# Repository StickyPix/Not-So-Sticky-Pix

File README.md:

# StickyPix

StickyPix is a small, rechargeable e-paper picture frame that lets you send
images from a phone or desktop app over Bluetooth Low Energy. The same product
family supports a four-gray black-and-white display and a six-color display.

## Image gallery

<table>
  <tr>
    <td></td>
    <td></td>
    <td></td>
  </tr>
  <tr>
    <td></td>
    <td></td>
    <td></td>
  </tr>
  <tr>
    <td></td>
    <td></td>
    <td></td>
  </tr>
</table>

## What is in this repository?

StickyPix is developed as a complete hardware and software product:

| Area | Contents |
| --- | --- |
| App | Flutter image editor, dithering previews, device management, and BLE image transfer |
| Firmware | Zephyr-based firmware for four-gray and six-color display variants |
| Hardware | KiCad schematics, PCBs, fabrication outputs, and bills of materials |
| Enclosure | Blender source files and printable STL parts for the bezel, rear shell, inner enclosure, and kickstand |
| Images | Prototype photos and product renders |

## How it works

1. Choose an image in the Flutter app.
2. Crop, rotate, and adjust the image for the selected device.
3. The app converts the image to the display's limited palette using dithering.
4. The processed framebuffer is sent to the device over BLE.
5. The device refreshes the e-paper panel and returns transfer progress and battery information.

The image pipeline currently supports:

- Four-gray output for the black-and-white display variant.
- Six-color output for black, white, yellow, red, blue, and green.
- Portrait and landscape editing for the six-color device.
- Packed framebuffer transfer sized for the target panel.

## Display variants

- [Six-color display / Spectra 6 panel](https://www.ebay.com/itm/267508191177?var=567305393025)
- [Black-and-white display panel](https://www.good-display.com/product/613.html)

The linked vendor pages are the reference parts for the current hardware
designs. Check the vendor documentation for the latest availability and
electrical specifications before ordering.

## JLCPCB fabrication settings

For the current PCB designs, I use the following JLCPCB configuration as the
fabrication reference:

| Setting | Value |
| --- | --- |
| Design | 1 |
| Delivery format | Single PCB |
| PCB thickness | 1.0 mm |
| PCB color | Green |
| Silkscreen | White |
| Material | FR4 TG135 |
| Surface finish | HASL (with lead) |
| Outer copper | 1 oz |
| Inner copper | 0.5 oz |
| Specify layer sequence | No |
| Specify stackup | Yes |
| Layer stackup | JLC04101H-3313 |

Treat this as the current ordering reference, not a guarantee that every board
revision uses the same stackup. Recheck the board layer count, dimensions, and
JLCPCB options before placing an order.

## Enclosure

The enclosure is split into a front bezel, rear shell, inner cardstock/support
piece, and kickstand. The repository includes both the editable Blender model
and exported STL files.

<table>
  <tr>
    <td></td>
    <td></td>
    <td></td>
  </tr>
</table>

## Repository layout

```text
Images/                         Prototype photos
3D Model/                       Printable enclosure STL files
Hardware/24p_bw_3p5/            Black-and-white KiCad design
Hardware/50p_spectra6_4/        Six-color KiCad design
Firmware/4GrayFinal/             Four-gray Zephyr firmware
Firmware/6ColorFinal/            Six-color Zephyr firmware
Flutter App/frontend/sticky_pix/ Flutter application
Manufacturing/                  Manufacturing files and BOM
```

## Project status

StickyPix is an active hardware prototype. The app, firmware, PCB designs, and
enclosure are included for development and iteration; dimensions, pinouts,
image timings, and manufacturing outputs may change.

## Development notes

The Flutter application is in `Flutter App/frontend/sticky_pix`. The firmware
projects use Zephyr and are kept separate so the four-gray and six-color panel
drivers can evolve independently. Build-tool-generated files and local SDK
paths should remain uncommitted.

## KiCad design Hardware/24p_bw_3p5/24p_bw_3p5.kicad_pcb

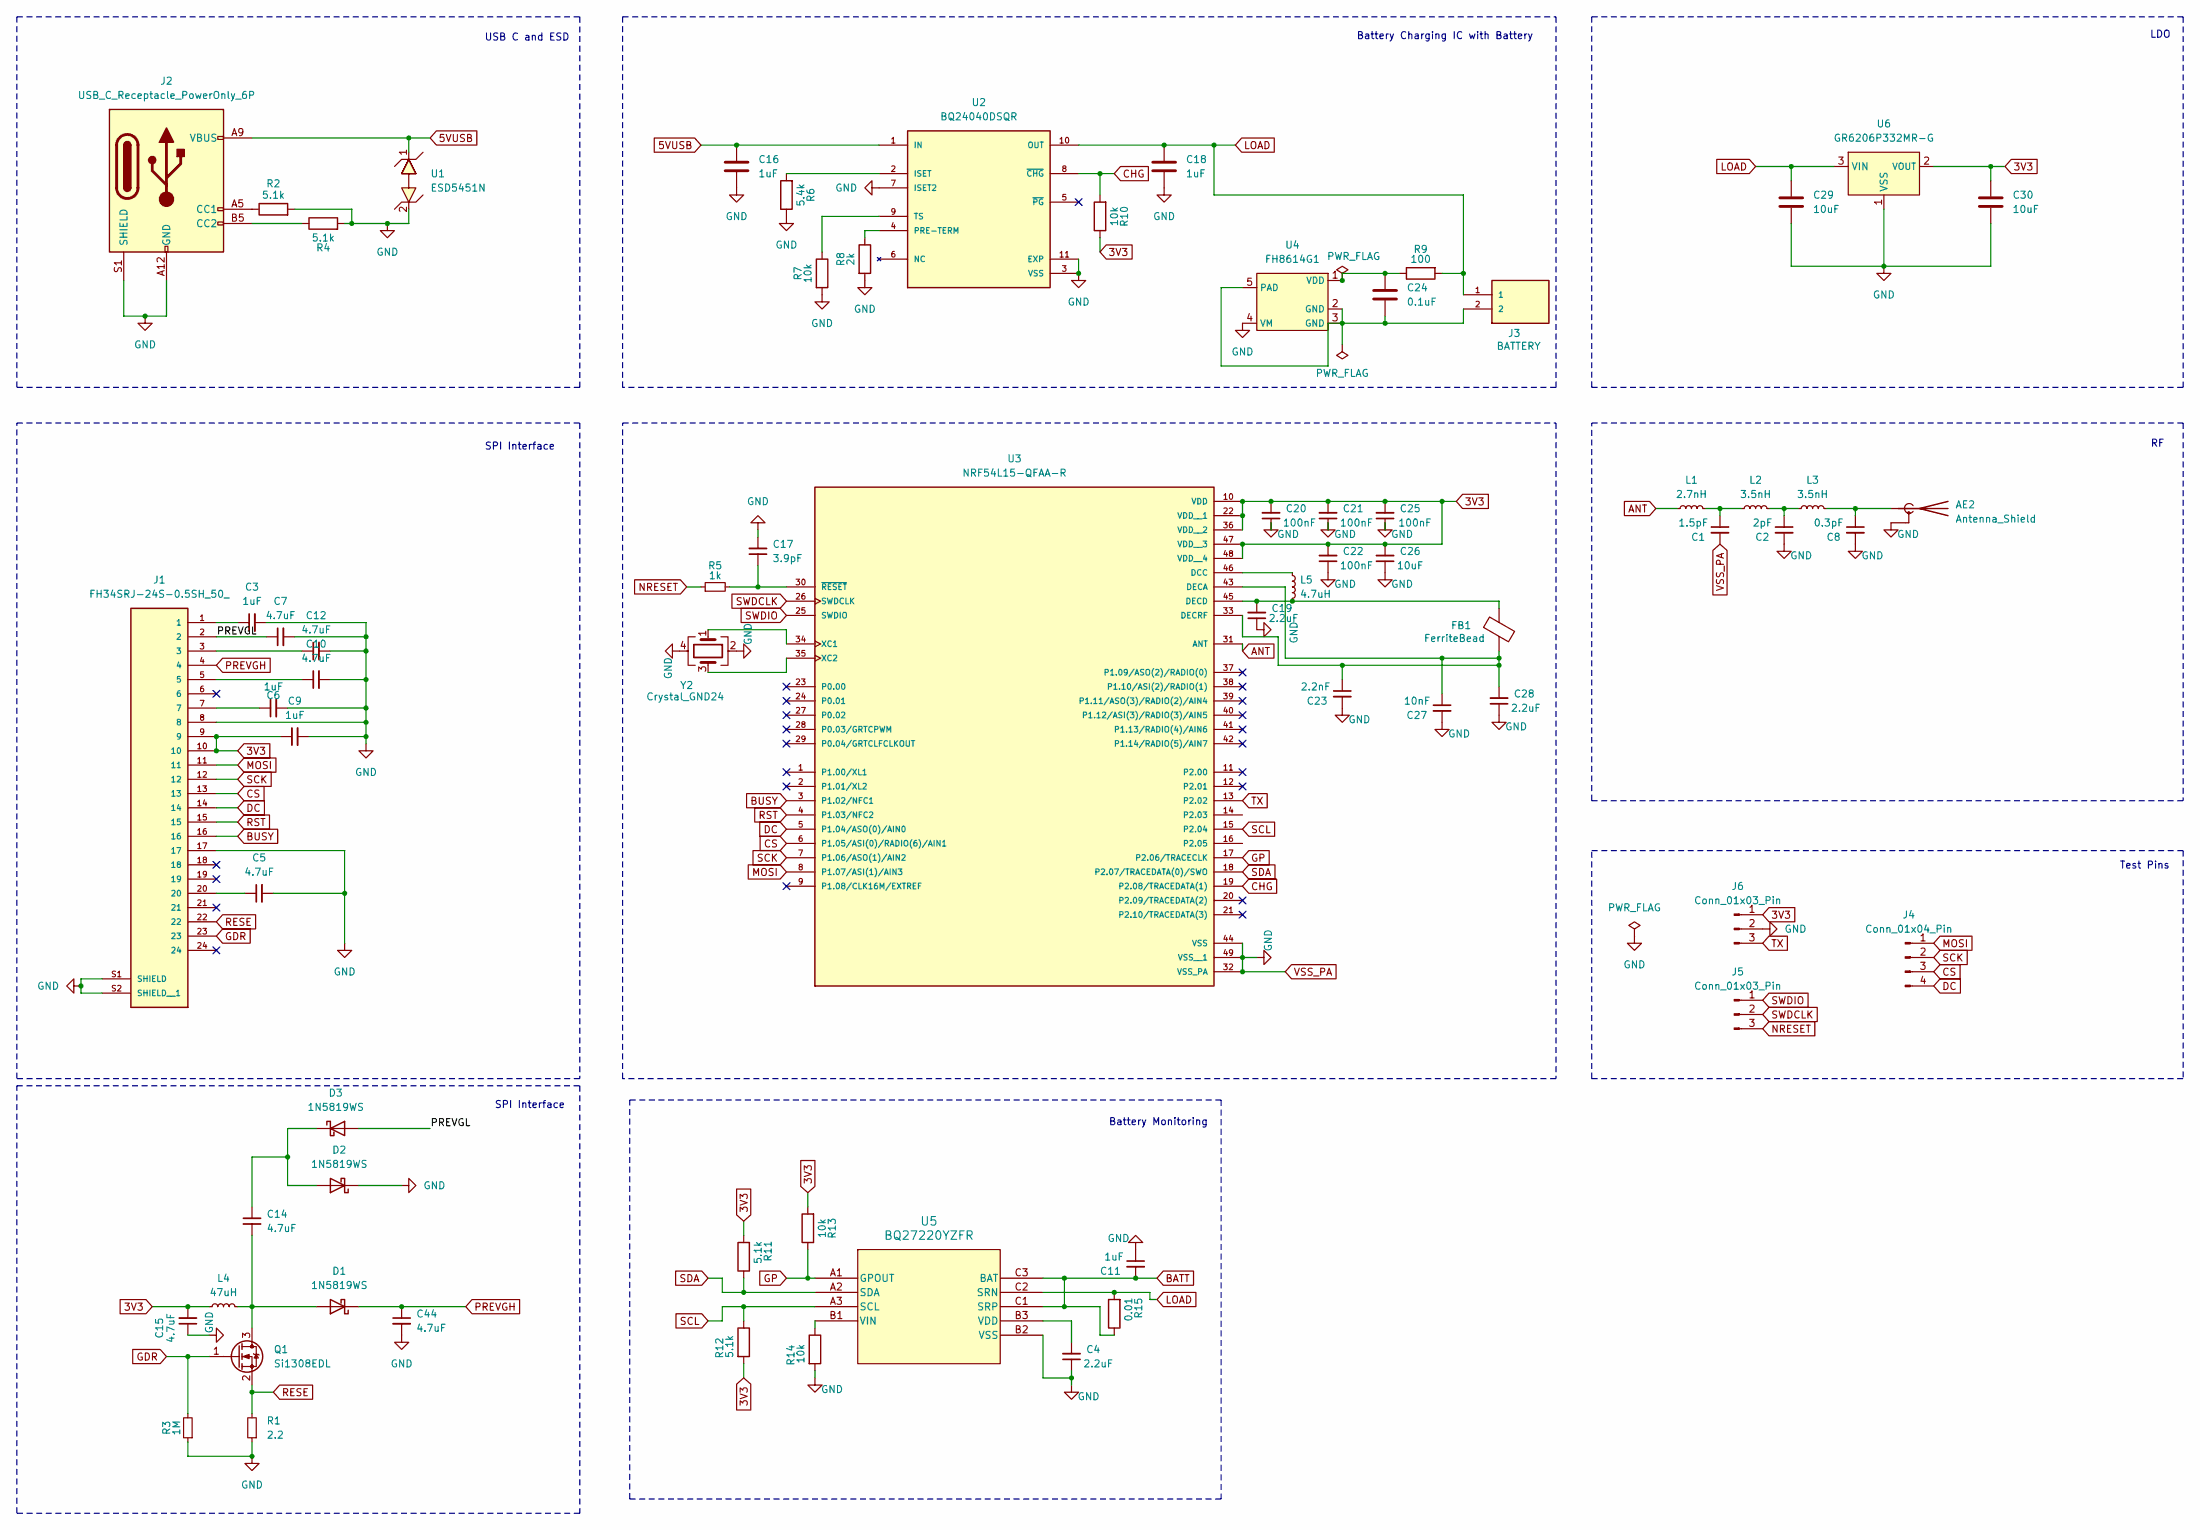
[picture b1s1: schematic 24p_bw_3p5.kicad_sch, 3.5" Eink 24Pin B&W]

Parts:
AE2: Antenna_Shield; 2.4GHz_Left_PC_ABS
C1: 1.5pF; RF_0201_0603Metric
C2: 2pF; RF_0201_0603Metric
C3, C6, C9: 1uF; C_0603_1608Metric
C4: 2.2uF; C_0402_1005Metric
C5, C7, C10, C12, C14, C15, C44: 4.7uF; C_0603_1608Metric
C8: 0.3pF; RF_0201_0603Metric
C11, C16, C18: 1uF; C_0402_1005Metric
C17: 3.9pF; C_0201_0603Metric
C19, C28: 2.2uF; C_0201_0603Metric
C20, C21, C22, C25: 100nF; C_0201_0603Metric
C23: 2.2nF; C_0201_0603Metric
C24: 0.1uF; C_0402_1005Metric
C26, C29, C30: 10uF; C_0402_1005Metric
C27: 10nF; C_0201_0603Metric
D1, D2, D3: 1N5819WS; D_SOD-323
FB1: FerriteBead; C_0201_0603Metric
J1: FH34SRJ-24S-0.5SH_50_; HRS_FH34SRJ-24S-0.5SH_50_
J2: USB_C_Receptacle_PowerOnly_6P; USB_C_SHOU_HAN_6P
J3: BATTERY; BATTERY_HC-1.2-2PWT
J4: Conn_01x04_Pin; PinHeader_1x04_P2.54mm_Vertical
J5, J6: Conn_01x03_Pin; PinHeader_1x03_P2.54mm_Vertical
L1: 2.7nH; RF_0201_0603Metric
L2, L3: 3.5nH; RF_0201_0603Metric
L4: 47uH; L_Cenker_CKCS3012
L5: 4.7uH; L_0603_1608Metric
Q1: Si1308EDL; SOT-323_SC-70
R1: 2.2; R_0402_1005Metric
R2, R4, R11, R12: 5.1k; R_0402_1005Metric
R3: 1M; R_0402_1005Metric
R5: 1k; R_0201_0603Metric
R6: 5.4k; R_0402_1005Metric
R7, R10, R13, R14: 10k; R_0402_1005Metric
R8: 2k; R_0402_1005Metric
R9: 100; R_0402_1005Metric
R15: 0.01; R_0402_1005Metric
U1: ESD5451N; DFN1006-2
U2: BQ24040DSQR; IC_BQ24045DSQR; PARTREV H
U3: NRF54L15-QFAA-R; QFN40P600X600X90-49N; PARTREV 0.8
U4: FH8614G1; UDFN-4-1EP_1x1mm_P0.65mm_EP0.48x0.48mm
U5: BQ27220YZFR; BGA9C50P3X3_158X162X62
U6: GR6206P332MR-G; SOT-23-3
Y2: Crystal_GND24; Crystal_SMD_2016-4Pin_2.0x1.6mm

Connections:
3V3: C9.1, C15.2, C20.2, C21.2, C22.2, C25.2, C26.2, C30.1, J1.9, J1.10, J6.1, L4.1, R10.1, R11.2, R12.2, R13.2, U3.10 (VDD), U3.22 (VDD__1), U3.36 (VDD__2), U3.47 (VDD__3), U3.48 (VDD__4), U6.2 (VOUT)
5VUSB: C16.1, J2.A9 (VBUS), J2.B9 (VBUS), U1.1, U2.1 (IN)
/PREVGL: C7.1, D3.2 (A), J1.2
ANT: L1.1, U3.31 (ANT)
BATT: C11.2, R15.1, U5.C1 (SRP), U5.C3 (BAT)
BUSY: J1.16, U3.3 (P1.02/NFC1)
CHG: R10.2, U2.8 (~CHG), U3.19 (P2.08/TRACEDATA(1))
CS: J1.13, J4.3, U3.6 (P1.05/ASI(0)/RADIO(6)/AIN1)
DC: J1.14, J4.4, U3.5 (P1.04/ASO(0)/AIN0)
GDR: J1.23, Q1.1 (G), R3.2
GP: R13.1, U3.17 (P2.06/TRACECLK), U5.A1 (GPOUT)
LOAD: C18.1, C29.1, J3.1, R9.2, R15.2, U2.10 (OUT), U5.C2 (SRN), U6.3 (VIN)
MOSI: J1.11, J4.1, U3.8 (P1.07/ASI(1)/AIN3)
NRESET: J5.3, R5.1
unnamed: AE2.1 (A), C8.1, L3.2
unnamed: C1.1, L1.2, L2.1
unnamed: C2.1, L2.2, L3.1
unnamed: C3.1, J1.1
unnamed: C5.1, J1.20
unnamed: C6.1, J1.7
unnamed: C10.1, J1.5
unnamed: C12.1, J1.3
unnamed: C14.2, D1.2 (A), L4.2, Q1.3 (D)
unnamed: C14.1, D2.2 (A), D3.1 (K)
unnamed: J2.A5 (CC1), R2.1
unnamed: J2.B5 (CC2), R4.1
unnamed: R6.2, U2.2 (ISET)
unnamed: R8.1, U2.4 (PRE-TERM)
unnamed: R7.1, U2.9 (TS)
unnamed: L5.1, U3.46 (DCC)
unnamed: C23.1, C27.1, C28.2, FB1.2, U3.33 (DECRF), U3.43 (DECA)
unnamed: C19.2, FB1.1, L5.2, U3.45 (DECD)
unnamed: U3.34 (XC1), Y2.1
unnamed: U3.35 (XC2), Y2.3
unnamed: C17.1, R5.2, U3.30 (~RESET)
unnamed: C24.2, J3.2, U4.2 (GND), U4.3 (GND), U4.5 (PAD)
unnamed: C24.1, R9.1, U4.1 (VDD)
unnamed: C4.2, U5.B3 (VDD)
unnamed: R14.1, U5.B1 (VIN)
PREVGH: C44.1, D1.1 (K), J1.4
RESE: J1.22, Q1.2 (S), R1.2
RST: J1.15, U3.4 (P1.03/NFC2)
SCK: J1.12, J4.2, U3.7 (P1.06/ASO(1)/AIN2)
SCL: R12.1, U3.15 (P2.04), U5.A3 (SCL)
SDA: R11.1, U3.18 (P2.07/TRACEDATA(0)/SWO), U5.A2 (SDA)
SWDCLK: J5.2, U3.26 (SWDCLK)
SWDIO: J5.1, U3.25 (SWDIO)
TX: J6.3, U3.13 (P2.02)
VSS_PA: AE2.2 (Shield), C1.2, C2.2, C3.2, C4.1, C5.2, C6.2, C7.2, C8.2, C9.2, C10.2, C11.1, C12.2, C15.1, C16.2, C17.2, C18.2, C19.1, C20.1, C21.1, C22.1, C23.2, C25.1, C26.1, C27.2, C28.1, C29.2, C30.2, C44.2, D2.1 (K), J1.8, J1.17, J1.S1 (SHIELD), J1.S2 (SHIELD__1), J2.A12 (GND), J2.B12 (GND), J2.S1 (SHIELD), J6.2, R1.1, R2.2, R3.1, R4.2, R6.1, R7.2, R8.2, R14.2, U1.2, U2.3 (VSS), U2.7 (ISET2), U2.11 (EXP), U3.32 (VSS_PA), U3.44 (VSS), U3.49 (VSS__1), U4.4 (VM), U5.B2 (VSS), U6.1 (VSS), Y2.2, Y2.4

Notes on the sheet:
Test Pins
Battery Monitoring
Battery Charging IC with Battery
SPI Interface
LDO
USB C and ESD

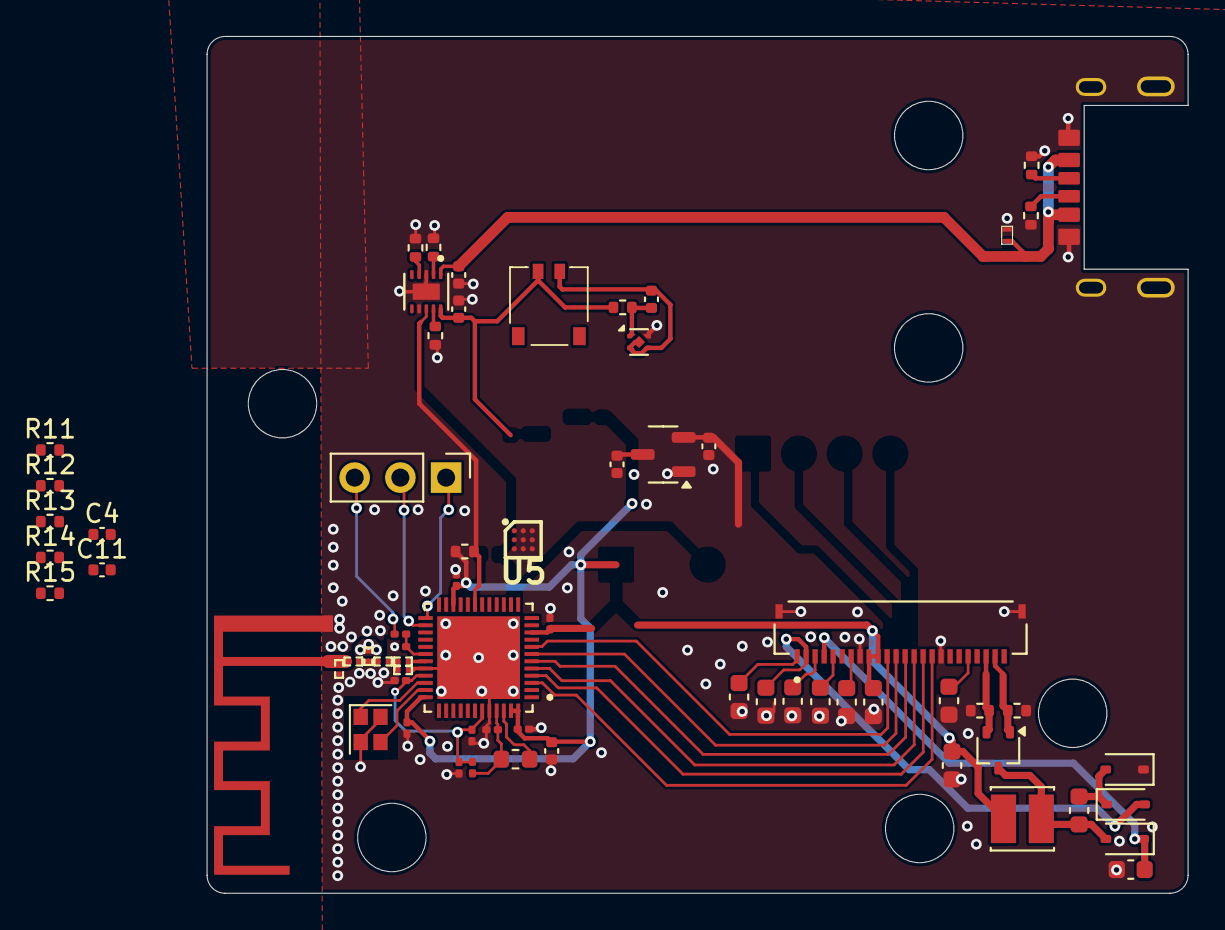
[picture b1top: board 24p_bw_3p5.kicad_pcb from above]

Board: 4 copper layers, 54.5 x 47.6 mm, 67 parts (0 on the bottom side), 48 nets.

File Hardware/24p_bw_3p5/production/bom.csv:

Designator,Footprint,Quantity,Value,LCSC Part #
AE2,2.4GHz_Left_PC_ABS,1,Antenna_Shield,
C1,0201,1,1.5pF,
"C10, C12, C14, C15, C44, C5, C7",0603,7,4.7uF,
"C16, C18",0402,2,1uF,
C17,0201,1,3.9pF,
"C19, C28",0201,2,2.2uF,
C2,0201,1,2pF,
"C20, C21, C22, C25",0201,4,100nF,
C23,0201,1,2.2nF,
C24,0402,1,0.1uF,
"C26, C29, C30",0402,3,10uF,
C27,0201,1,10nF,
"C3, C6, C9",0603,3,1uF,
C8,0201,1,0.3pF,
"D1, D2, D3",D_SOD-323,3,1N5819WS,
FB1,0201,1,FerriteBead,
J1,HRS_FH34SRJ-24S-0.5SH_50_,1,FH34SRJ-24S-0.5SH_50_,
J2,USB_C_SHOU_HAN_6P,1,USB_C_Receptacle_PowerOnly_6P,
J3,BATTERY_HC-1.2-2PWT,1,BATTERY,
J4,PinHeader_1x04_P2.54mm_Vertical,1,Conn_01x04_Pin,
"J5, J6",PinHeader_1x03_P2.54mm_Vertical,2,Conn_01x03_Pin,
L1,0201,1,2.7nH,
"L2, L3",0201,2,3.5nH,
L4,L_Cenker_CKCS3012,1,47uH,
L5,0603,1,4.7uH,
Q1,SOT-323_SC-70,1,Si1308EDL,
R1,0402,1,2.2,
"R10, R7",0402,2,10k,
"R2, R4",0402,2,5.1k,
R3,0402,1,1M,
R5,0201,1,1k,
R6,0402,1,5.4k,
R8,0402,1,2k,
R9,0402,1,100,
U1,DFN1006-2,1,ESD5451N,
U2,IC_BQ24045DSQR,1,BQ24040DSQR,
U3,QFN40P600X600X90-49N,1,NRF54L15-QFAA-R,
U4,UDFN-4-1EP_1x1mm_P0.65mm_EP0.48x0.48mm,1,FH8614G1,
U6,SOT-23-3,1,GR6206P332MR-G,
Y2,Crystal_SMD_2016-4Pin_2.0x1.6mm,1,Crystal_GND24,
